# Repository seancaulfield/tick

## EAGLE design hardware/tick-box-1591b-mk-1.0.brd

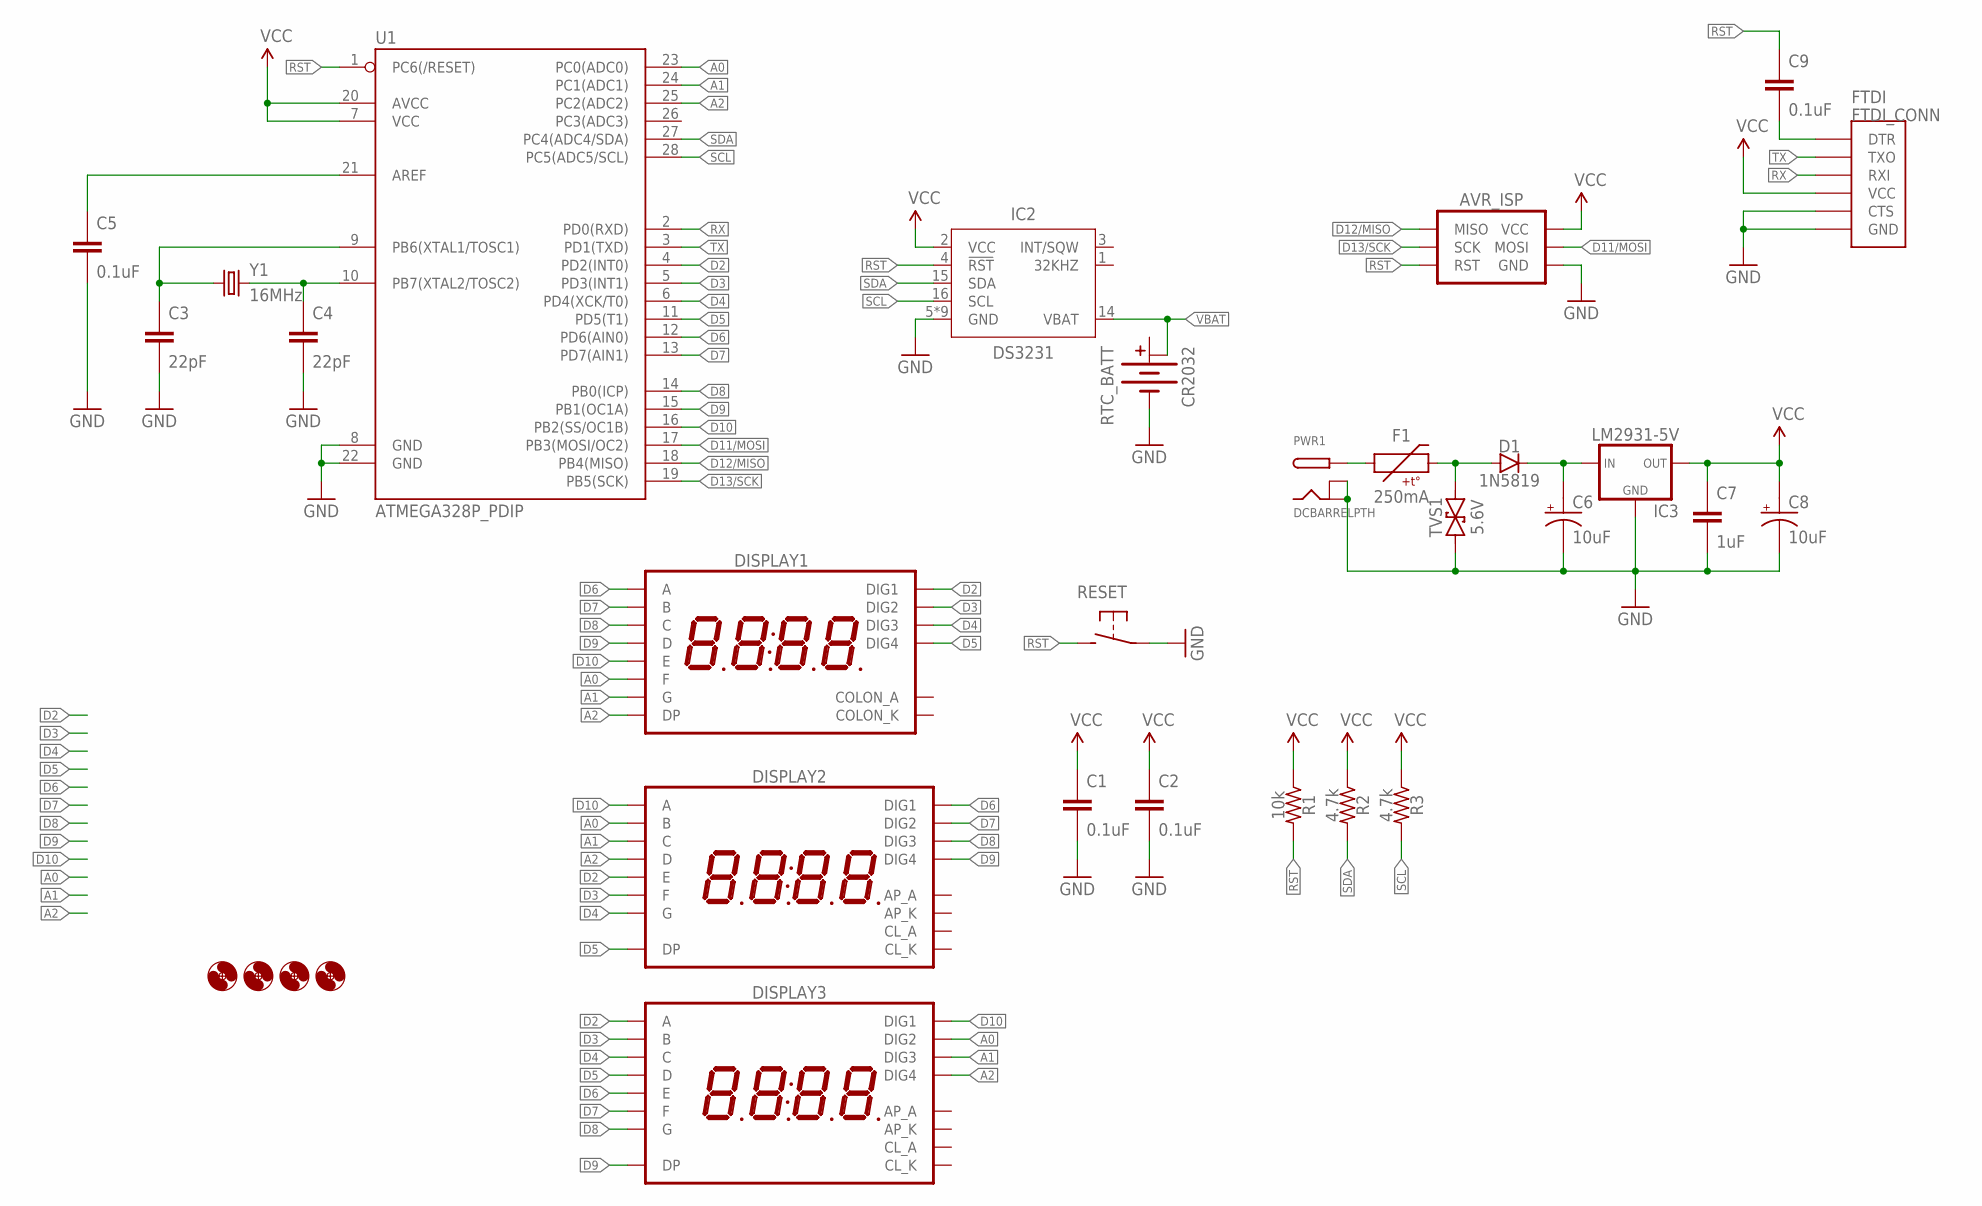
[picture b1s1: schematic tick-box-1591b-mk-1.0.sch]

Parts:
AVR_ISP: AVR_SPI_PRG_6PTH; 2X3
C1, C2, C5, C9: 0.1uF; C025-024X044
C3, C4: 22pF; C025-024X044
C6, C8: 10uF; E2-5
C7: 1uF; C025-024X044
D1: 1N5819; DIODE-10.16MM
DISPLAY1: 7SEG_4DIGIT_COLON14.2MM-CC-NS; 7SEG_4DIG_NS
DISPLAY2, DISPLAY3: 7SEG_4DIGIT_COLON_APOS; 7SEG_4DIG_10MM
F1: 250mA; PTC-PTH-5.08MM
FTDI: FTDI_CONN
H1, H2, H3, H4: HOLE#2; HOLE-#2
IC2: DS3231; SO16W
IC3: LM2931-5V; TO220-IGO-THERMPAD
PWR1: DCBARRELPTH; DCJACK_2MM_PTH
R1: 10k; RESISTOR-AXIAL-PTH-7.62MM
R2, R3: 4.7k; RESISTOR-AXIAL-PTH-7.62MM
RESET: SPST-NO-TACT6MM-PTH-SMALL-PADS; DTS-6-SMALL-PADS
RTC_BATT: CR2032; BATTCON_20MM_MINE
TVS1: 5.6V; DO-41-TVS
U1: ATMEGA328P_PDIP; DIL28-3
Y1: 16MHz; HC49U-V

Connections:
A0: DISPLAY1.P$12 (F), DISPLAY2.16 (B), DISPLAY3.2 (DIG2), U1.23 (PC0(ADC0))
A1: DISPLAY1.P$5 (G), DISPLAY2.13 (C), DISPLAY3.6 (DIG3), U1.24 (PC1(ADC1))
A2: DISPLAY1.P$3 (DP), DISPLAY2.3 (D), DISPLAY3.8 (DIG4), U1.25 (PC2(ADC2))
D2: DISPLAY1.P$14 (DIG1), DISPLAY2.5 (E), DISPLAY3.14 (A), U1.4 (PD2(INT0))
D3: DISPLAY1.P$11 (DIG2), DISPLAY2.11 (F), DISPLAY3.16 (B), U1.5 (PD3(INT1))
D4: DISPLAY1.P$10 (DIG3), DISPLAY2.15 (G), DISPLAY3.13 (C), U1.6 (PD4(XCK/T0))
D5: DISPLAY1.P$6 (DIG4), DISPLAY2.7 (DP), DISPLAY3.3 (D), U1.11 (PD5(T1))
D6: DISPLAY1.P$13 (A), DISPLAY2.1 (DIG1), DISPLAY3.5 (E), U1.12 (PD6(AIN0))
D7: DISPLAY1.P$9 (B), DISPLAY2.2 (DIG2), DISPLAY3.11 (F), U1.13 (PD7(AIN1))
D8: DISPLAY1.P$4 (C), DISPLAY2.6 (DIG3), DISPLAY3.15 (G), U1.14 (PB0(ICP))
D9: DISPLAY1.P$2 (D), DISPLAY2.8 (DIG4), DISPLAY3.7 (DP), U1.15 (PB1(OC1A))
D10: DISPLAY1.P$1 (E), DISPLAY2.14 (A), DISPLAY3.1 (DIG1), U1.16 (PB2(SS/OC1B))
D11/MOSI: AVR_ISP.4 (MOSI), U1.17 (PB3(MOSI/OC2))
D12/MISO: AVR_ISP.1 (MISO), U1.18 (PB4(MISO))
D13/SCK: AVR_ISP.3 (SCK), U1.19 (PB5(SCK))
GND: AVR_ISP.6 (GND), C1.2, C2.2, C3.2, C4.2, C5.2, C6.-, C7.2, C8.-, FTDI.CTS, FTDI.GND, IC2.5 (GND), IC2.6 (GND), IC2.7 (GND), IC2.8 (GND), IC2.9 (GND), IC2.10 (GND), IC2.11 (GND), IC2.12 (GND), IC2.13 (GND), IC3.4 (GND), IC3.GND, PWR1.BRK, PWR1.GND, RESET.1, RESET.2 (1), RTC_BATT.BOTTOM (-), TVS1.P$1 (1), U1.8 (GND), U1.22 (GND)
unnamed: C4.1, U1.10 (PB7(XTAL2/TOSC2)), Y1.2
unnamed: C3.1, U1.9 (PB6(XTAL1/TOSC1)), Y1.1
unnamed: C6.+, D1.C, IC3.IN
unnamed: F1.P$1 (1), PWR1.PWR
unnamed: C5.1, U1.21 (AREF)
unnamed: D1.A, F1.P$2 (2), TVS1.P$2 (2)
unnamed: C9.2, FTDI.DTR
RST: AVR_ISP.5 (RST), C9.1, IC2.4 (!RST), R1.P$2 (2), RESET.3 (2), RESET.4 (2), U1.1 (PC6(/RESET))
RX: FTDI.RXI, U1.2 (PD0(RXD))
SCL: IC2.16 (SCL), R3.P$2 (2), U1.28 (PC5(ADC5/SCL))
SDA: IC2.15 (SDA), R2.P$2 (2), U1.27 (PC4(ADC4/SDA))
TX: FTDI.TXO, U1.3 (PD1(TXD))
VBAT: IC2.14 (VBAT), RTC_BATT.TOP@2 (+1)
VCC: AVR_ISP.2 (VCC), C1.1, C2.1, C7.1, C8.+, FTDI.VCC, IC2.2 (VCC), IC3.OUT, R1.P$1 (1), R2.P$1 (1), R3.P$1 (1), U1.7 (VCC), U1.20 (AVCC)

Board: 2 copper layers, 31 parts (1 on the bottom side), 30 nets, no tracks yet.

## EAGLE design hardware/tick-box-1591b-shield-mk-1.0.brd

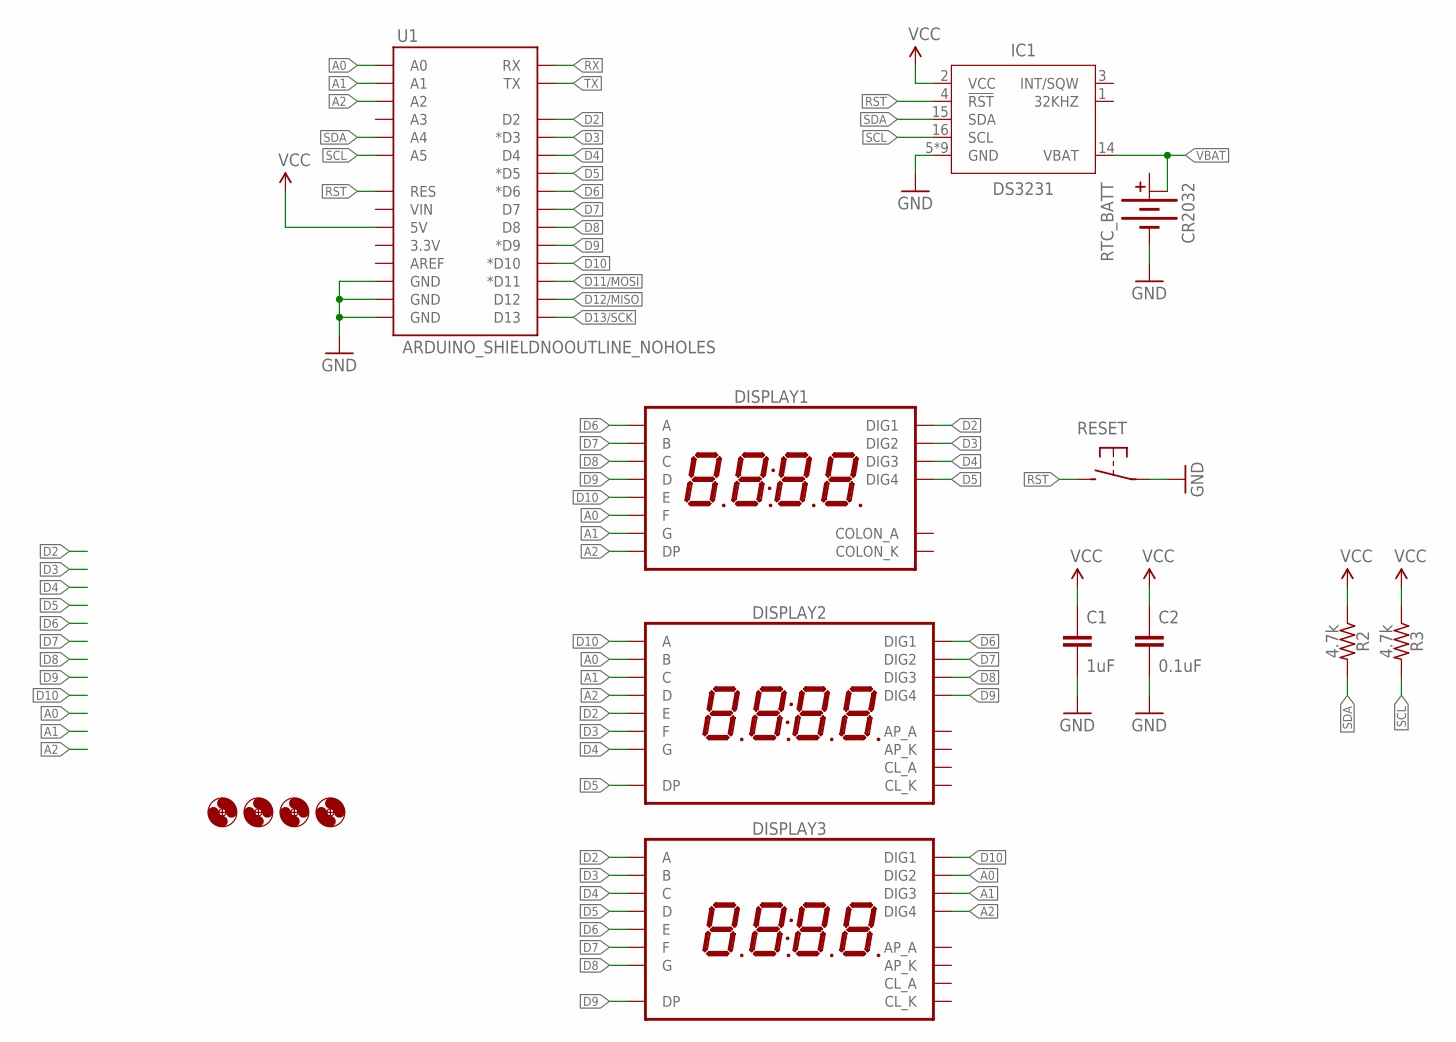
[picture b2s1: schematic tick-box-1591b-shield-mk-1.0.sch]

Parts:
C1: 1uF; C025-024X044
C2: 0.1uF; C025-024X044
DISPLAY1: 7SEG_4DIGIT_COLON14.2MM-CC-NS; 7SEG_4DIG_NS
DISPLAY2, DISPLAY3: 7SEG_4DIGIT_COLON_APOS; 7SEG_4DIG_10MM
H1, H2, H3, H4: HOLE#2; HOLE-#2
IC1: DS3231; SO16W
R2, R3: 4.7k; RESISTOR-AXIAL-PTH-7.62MM
RESET: SPST-NO-TACT6MM-PTH-SMALL-PADS; DTS-6-SMALL-PADS
RTC_BATT: CR2032; BATTCON_20MM_MINE
U1: ARDUINO_SHIELDNOOUTLINE_NOHOLES; ARDUINO_SHIELD_NOOUTLINE_NOHOLES

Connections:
A0: DISPLAY1.P$12 (F), DISPLAY2.16 (B), DISPLAY3.2 (DIG2), U1.A0
A1: DISPLAY1.P$5 (G), DISPLAY2.13 (C), DISPLAY3.6 (DIG3), U1.A1
A2: DISPLAY1.P$3 (DP), DISPLAY2.3 (D), DISPLAY3.8 (DIG4), U1.A2
D2: DISPLAY1.P$14 (DIG1), DISPLAY2.5 (E), DISPLAY3.14 (A), U1.D2
D3: DISPLAY1.P$11 (DIG2), DISPLAY2.11 (F), DISPLAY3.16 (B), U1.D3 (*D3)
D4: DISPLAY1.P$10 (DIG3), DISPLAY2.15 (G), DISPLAY3.13 (C), U1.D4
D5: DISPLAY1.P$6 (DIG4), DISPLAY2.7 (DP), DISPLAY3.3 (D), U1.D5 (*D5)
D6: DISPLAY1.P$13 (A), DISPLAY2.1 (DIG1), DISPLAY3.5 (E), U1.D6 (*D6)
D7: DISPLAY1.P$9 (B), DISPLAY2.2 (DIG2), DISPLAY3.11 (F), U1.D7
D8: DISPLAY1.P$4 (C), DISPLAY2.6 (DIG3), DISPLAY3.15 (G), U1.D8
D9: DISPLAY1.P$2 (D), DISPLAY2.8 (DIG4), DISPLAY3.7 (DP), U1.D9 (*D9)
D10: DISPLAY1.P$1 (E), DISPLAY2.14 (A), DISPLAY3.1 (DIG1), U1.D10 (*D10)
D11/MOSI: U1.D11 (*D11)
D12/MISO: U1.D12
D13/SCK: U1.D13
GND: C1.2, C2.2, IC1.5 (GND), IC1.6 (GND), IC1.7 (GND), IC1.8 (GND), IC1.9 (GND), IC1.10 (GND), IC1.11 (GND), IC1.12 (GND), IC1.13 (GND), RESET.1, RESET.2 (1), RTC_BATT.BOTTOM (-), U1.GND@0 (GND), U1.GND@1 (GND), U1.GND@2 (GND)
RST: IC1.4 (!RST), RESET.3 (2), RESET.4 (2), U1.RES
RX: U1.RX
SCL: IC1.16 (SCL), R3.P$2 (2), U1.A5
SDA: IC1.15 (SDA), R2.P$2 (2), U1.A4
TX: U1.TX
VBAT: IC1.14 (VBAT), RTC_BATT.TOP@2 (+1)
VCC: C1.1, C2.1, IC1.2 (VCC), R2.P$1 (1), R3.P$1 (1), U1.5V

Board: 2 copper layers, 15 parts (0 on the bottom side), 18 nets, no tracks yet.

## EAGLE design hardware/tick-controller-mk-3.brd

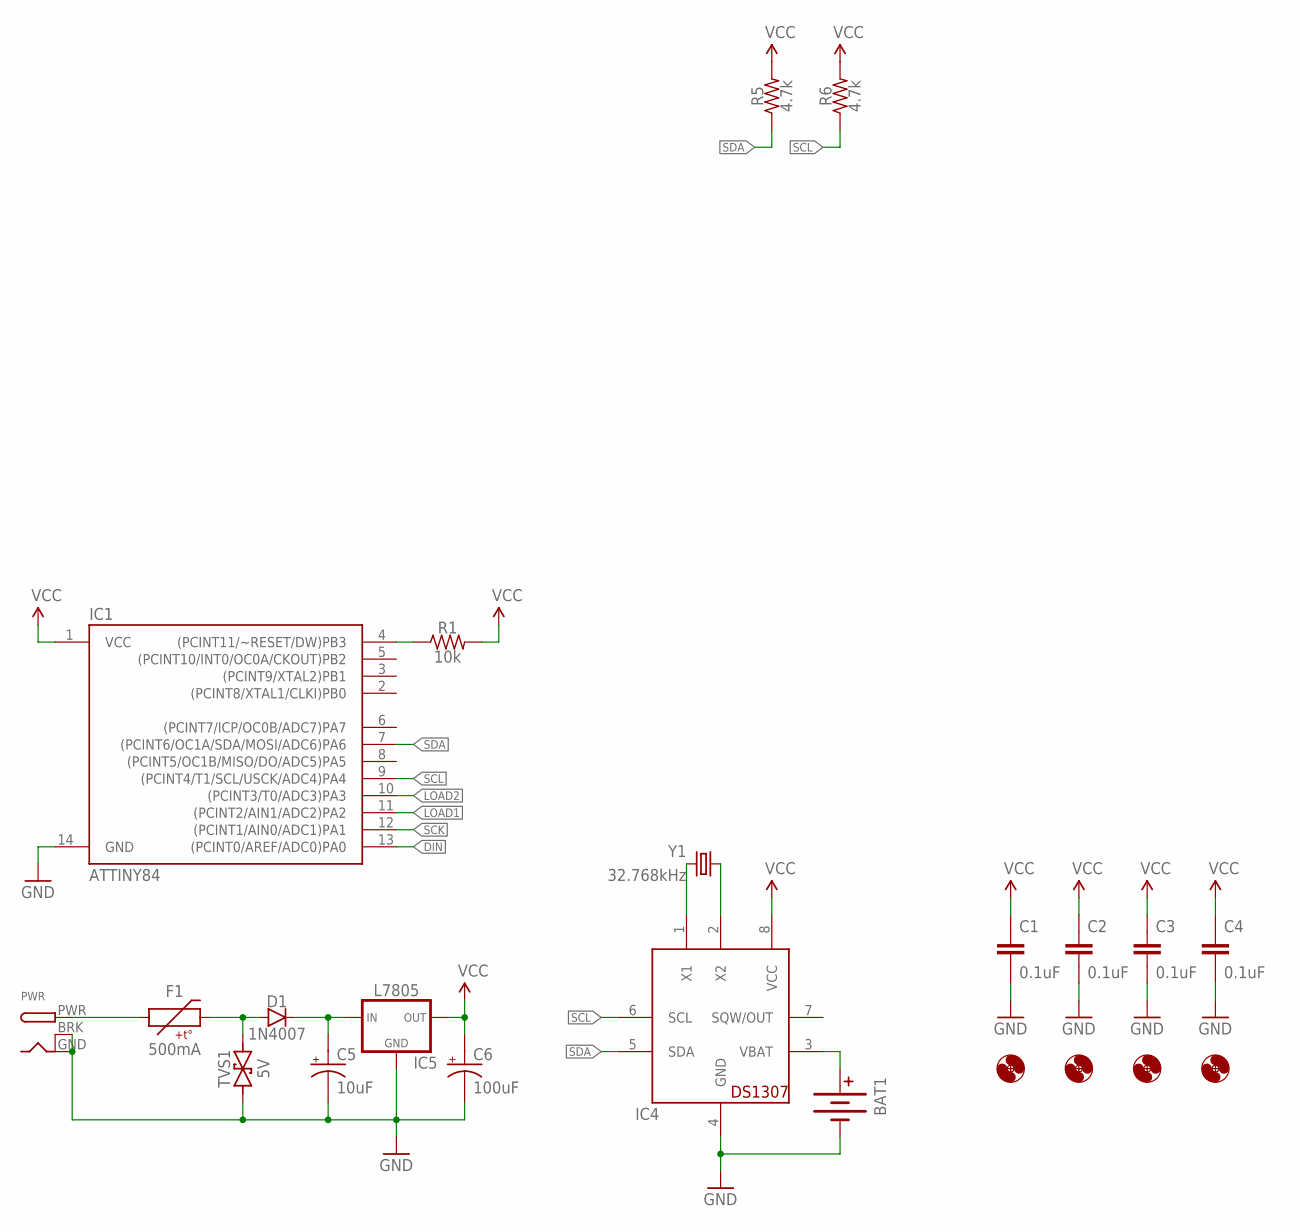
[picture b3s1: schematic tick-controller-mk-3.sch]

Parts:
BAT1: BATTERY20SMD; BATTCON_20MM
C1, C2, C3, C4: 0.1uF; C025-024X044
C5: 10uF; E2-5
C6: 100uF; E2-5
D1: 1N4007; DIODE-10.16MM
F1: 500mA; PTC-PTH-5.08MM
H1, H2, H3, H4: HOLE#2; HOLE-#2
IC1: ATTINY84; DIL14
IC4: DS1307; DIL08
IC5: L7805; TO-92-AMMO
PWR: DCBARRELPTH; DCJACK_2MM_PTH
R1: 10k; RESISTOR-AXIAL-PTH-5.08MM
R5, R6: 4.7k; RESISTOR-AXIAL-PTH-5.08MM
TVS1: 5V; DO-41-TVS-BI-10.16MM
Y1: 32.768kHz; TC26H

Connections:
DIN: IC1.13 ((PCINT0/AREF/ADC0)PA0)
GND: BAT1.2 (-), C1.2, C2.2, C3.2, C4.2, C5.-, C6.-, IC1.14 (GND), IC4.4 (GND), IC5.2 (GND), PWR.BRK, PWR.GND, TVS1.P$1 (1)
LOAD1: IC1.11 ((PCINT2/AIN1/ADC2)PA2)
LOAD2: IC1.10 ((PCINT3/T0/ADC3)PA3)
unnamed: IC1.4 ((PCINT11/~RESET/DW)PB3), R1.P$1 (1)
unnamed: IC4.1 (X1), Y1.2
unnamed: BAT1.1 (+), BAT1.3 (+), IC4.3 (VBAT)
unnamed: IC4.2 (X2), Y1.1
unnamed: C5.+, D1.C, IC5.1 (IN)
unnamed: F1.P$1 (1), PWR.PWR
unnamed: D1.A, F1.P$2 (2), TVS1.P$2 (2)
SCK: IC1.12 ((PCINT1/AIN0/ADC1)PA1)
SCL: IC1.9 ((PCINT4/T1/SCL/USCK/ADC4)PA4), IC4.6 (SCL), R6.P$1 (1)
SDA: IC1.7 ((PCINT6/OC1A/SDA/MOSI/ADC6)PA6), IC4.5 (SDA), R5.P$1 (1)
VCC: C1.1, C2.1, C3.1, C4.1, C6.+, IC1.1 (VCC), IC4.8 (VCC), IC5.3 (OUT), R1.P$2 (2), R5.P$2 (2), R6.P$2 (2)

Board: 2 copper layers, 22 parts (0 on the bottom side), 11 nets, no tracks yet.

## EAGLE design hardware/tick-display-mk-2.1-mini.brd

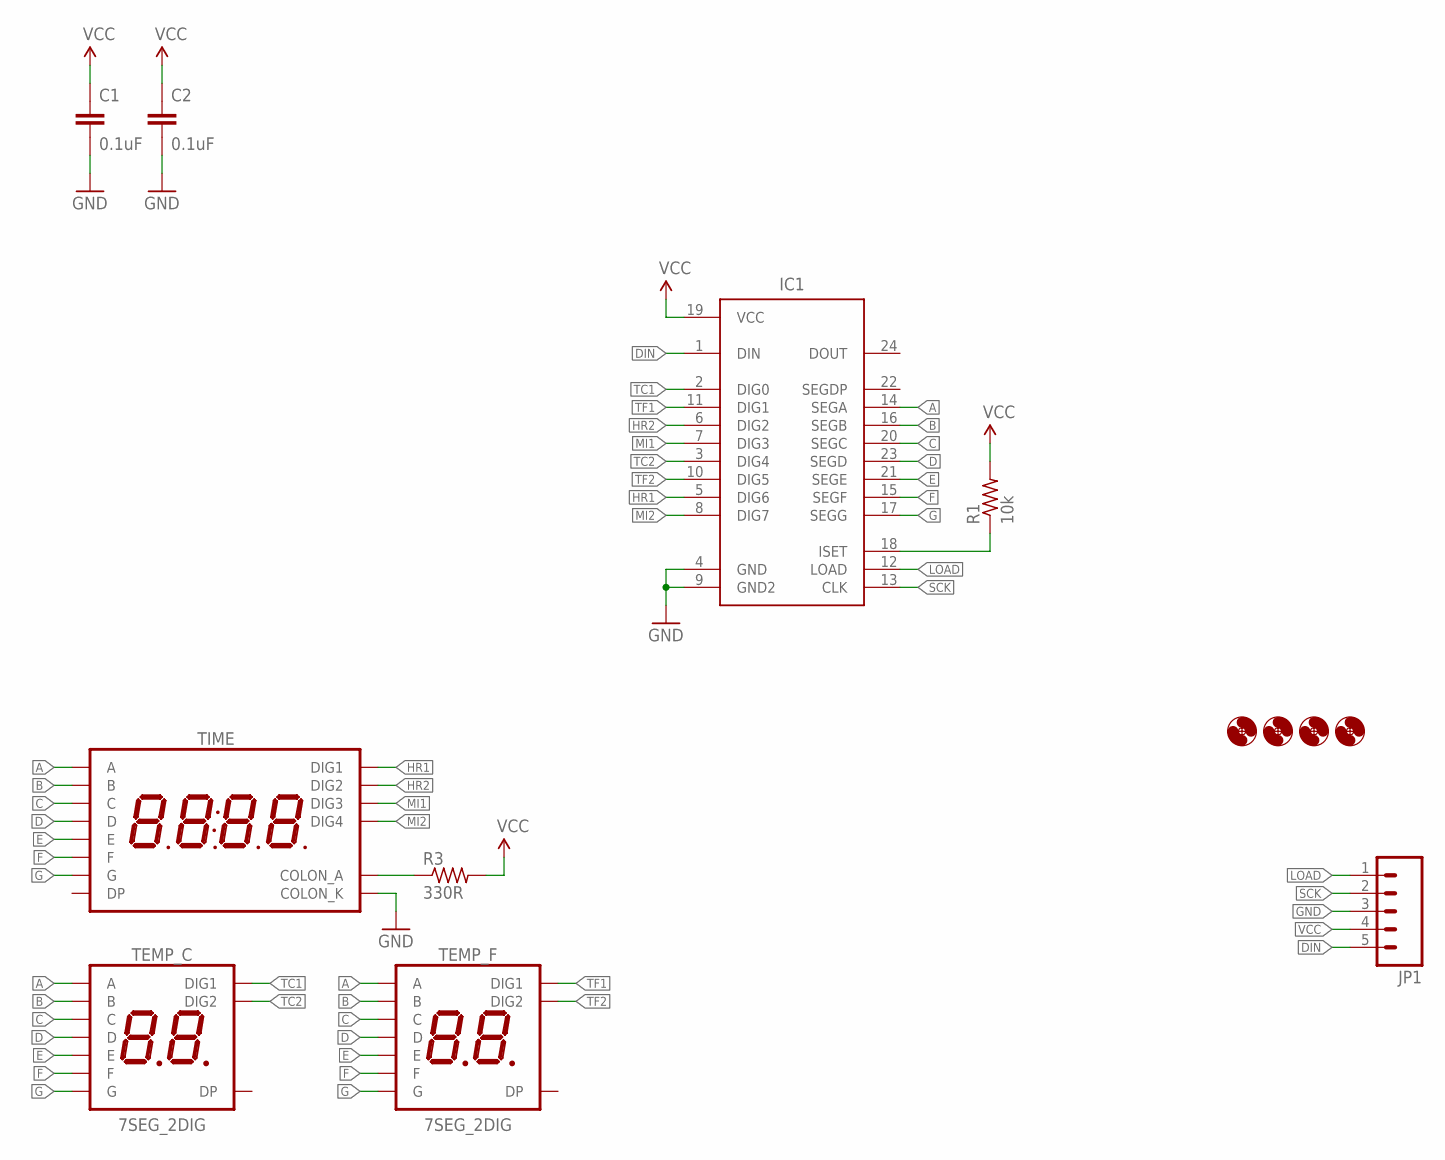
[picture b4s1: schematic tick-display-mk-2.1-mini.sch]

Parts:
C1, C2: 0.1uF; C025-024X044
H1, H2, H3, H4: HOLE#2; HOLE-#2
IC1: MAX7219DIP; DIL24
JP1: M05JST-PH-VERT-PTH; JST-5-PH-VERT-PTH
R1: 10k; RESISTOR-AXIAL-PTH-5.08MM
R3: 330R; RESISTOR-AXIAL-PTH-5.08MM
TEMP_C: 7SEG_2DIG; 7SEG_2DIG_14MM
TEMP_F: 7SEG_2DIG; 7SEG_2DIG_14MM
TIME: 7SED_4DIGIT_14MM14.2MM-CC; 7SEG_4DIG

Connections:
A: IC1.14 (SEGA), TEMP_C.4 (A), TEMP_F.4 (A), TIME.P$13 (A)
B: IC1.16 (SEGB), TEMP_C.3 (B), TEMP_F.3 (B), TIME.P$9 (B)
C: IC1.20 (SEGC), TEMP_C.9 (C), TEMP_F.9 (C), TIME.P$4 (C)
D: IC1.23 (SEGD), TEMP_C.8 (D), TEMP_F.8 (D), TIME.P$2 (D)
DIN: IC1.1 (DIN), JP1.5
E: IC1.21 (SEGE), TEMP_C.6 (E), TEMP_F.6 (E), TIME.P$1 (E)
F: IC1.15 (SEGF), TEMP_C.7 (F), TEMP_F.7 (F), TIME.P$12 (F)
G: IC1.17 (SEGG), TEMP_C.1 (G), TEMP_F.1 (G), TIME.P$5 (G)
GND: C1.2, C2.2, IC1.4 (GND), IC1.9 (GND2), JP1.3, TIME.P$7 (COLON_K)
HR1: IC1.5 (DIG6), TIME.P$14 (DIG1)
HR2: IC1.6 (DIG2), TIME.P$11 (DIG2)
LOAD: IC1.12 (LOAD), JP1.1
MI1: IC1.7 (DIG3), TIME.P$10 (DIG3)
MI2: IC1.8 (DIG7), TIME.P$6 (DIG4)
unnamed: IC1.18 (ISET), R1.P$1 (1)
unnamed: R3.P$1 (1), TIME.P$8 (COLON_A)
SCK: IC1.13 (CLK), JP1.2
TC1: IC1.2 (DIG0), TEMP_C.5 (DIG1)
TC2: IC1.3 (DIG4), TEMP_C.10 (DIG2)
TF1: IC1.11 (DIG1), TEMP_F.5 (DIG1)
TF2: IC1.10 (DIG5), TEMP_F.10 (DIG2)
VCC: C1.1, C2.1, IC1.19 (VCC), JP1.4, R1.P$2 (2), R3.P$2 (2)

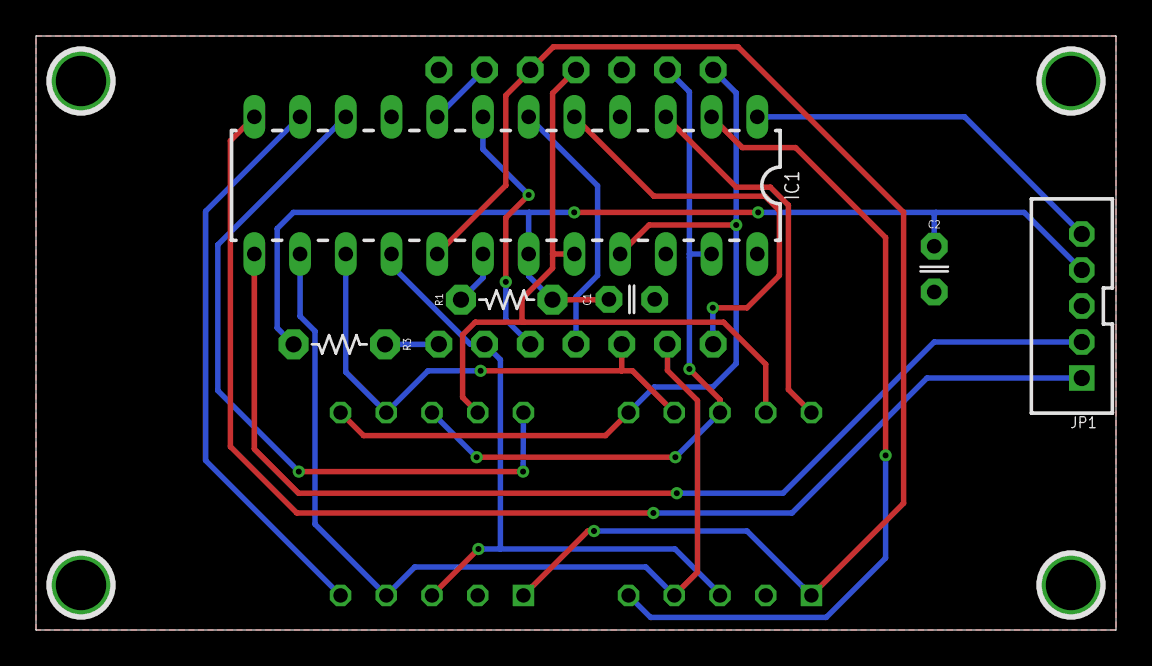
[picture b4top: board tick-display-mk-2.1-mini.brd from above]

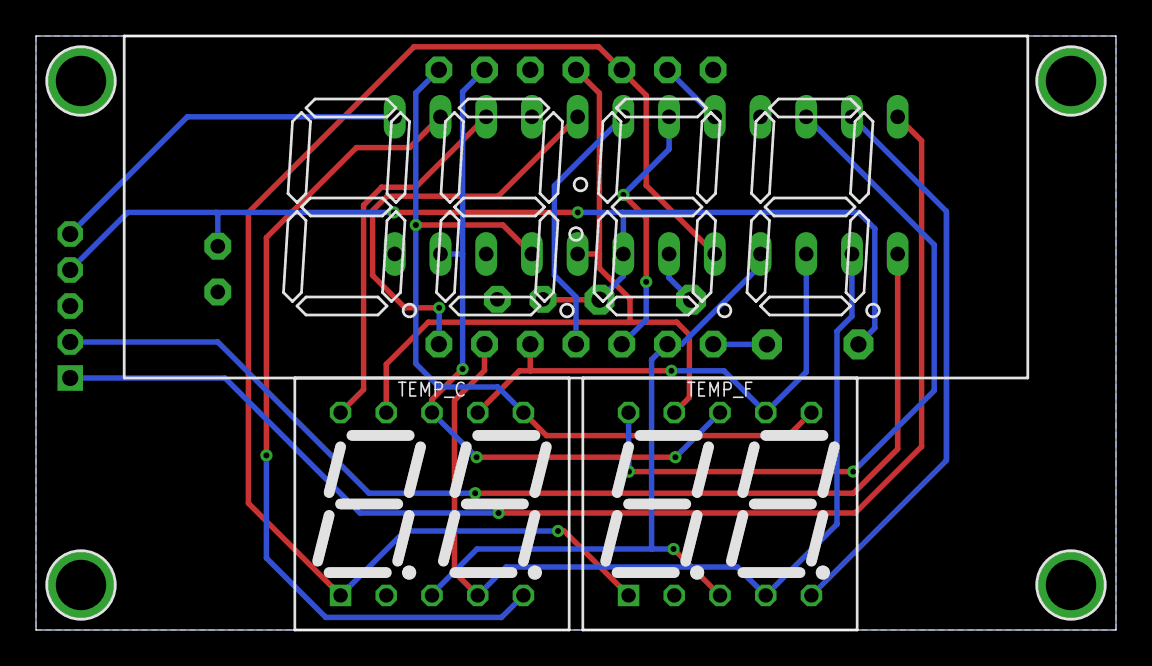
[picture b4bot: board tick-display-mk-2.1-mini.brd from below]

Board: 2 copper layers, 60.0 x 33.0 mm, 13 parts (3 on the bottom side), 22 nets.

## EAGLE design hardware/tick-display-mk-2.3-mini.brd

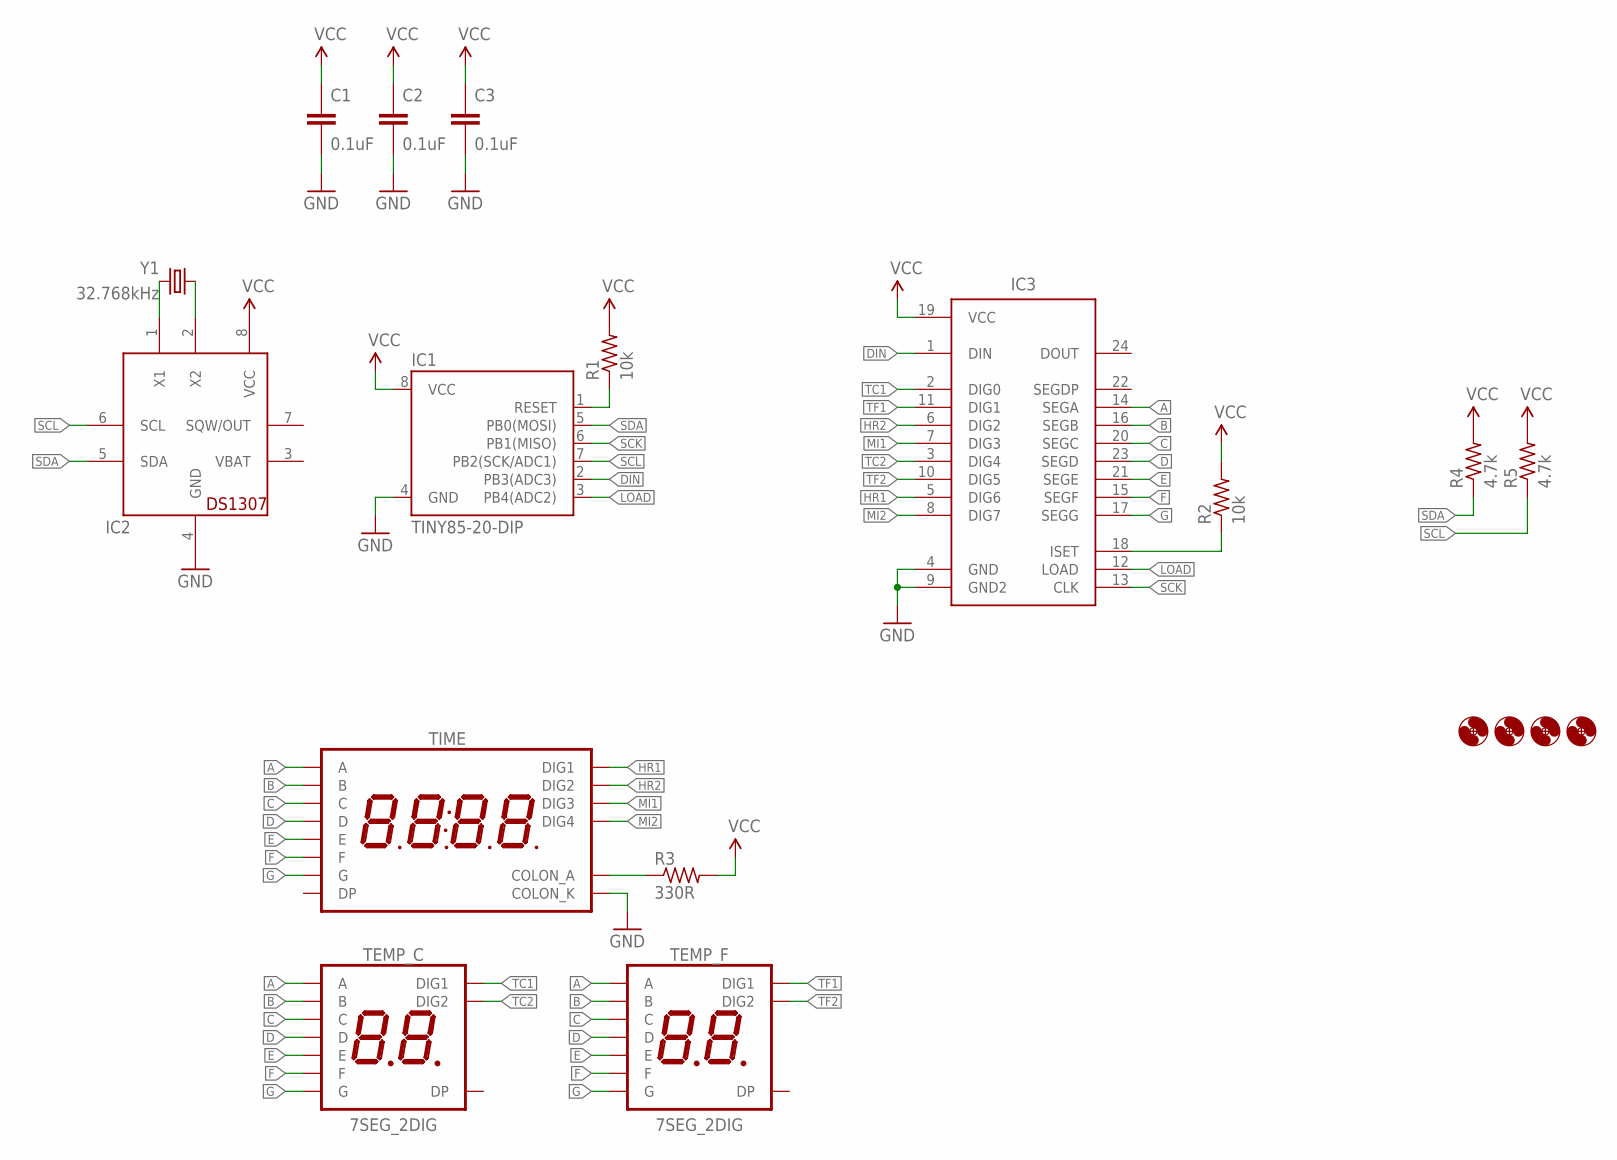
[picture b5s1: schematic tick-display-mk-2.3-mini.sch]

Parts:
C1, C2, C3: 0.1uF; C025-024X044
H1, H2, H3, H4: HOLE#2; HOLE-#2
IC1: TINY85-20-DIP; DIP08
IC2: DS1307; DIL08
IC3: MAX7219DIP; DIL24
R1, R2: 10k; RESISTOR-AXIAL-PTH-5.08MM
R3: 330R; RESISTOR-AXIAL-PTH-5.08MM
R4, R5: 4.7k; RESISTOR-AXIAL-PTH-5.08MM
TEMP_C: 7SEG_2DIG; 7SEG_2DIG_14MM
TEMP_F: 7SEG_2DIG; 7SEG_2DIG_14MM
TIME: 7SED_4DIGIT_14MM14.2MM-CC; 7SEG_4DIG
Y1: 32.768kHz; TC26H

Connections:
A: IC3.14 (SEGA), TEMP_C.4 (A), TEMP_F.4 (A), TIME.P$13 (A)
B: IC3.16 (SEGB), TEMP_C.3 (B), TEMP_F.3 (B), TIME.P$9 (B)
C: IC3.20 (SEGC), TEMP_C.9 (C), TEMP_F.9 (C), TIME.P$4 (C)
D: IC3.23 (SEGD), TEMP_C.8 (D), TEMP_F.8 (D), TIME.P$2 (D)
DIN: IC1.2 (PB3(ADC3)), IC3.1 (DIN)
E: IC3.21 (SEGE), TEMP_C.6 (E), TEMP_F.6 (E), TIME.P$1 (E)
F: IC3.15 (SEGF), TEMP_C.7 (F), TEMP_F.7 (F), TIME.P$12 (F)
G: IC3.17 (SEGG), TEMP_C.1 (G), TEMP_F.1 (G), TIME.P$5 (G)
GND: C1.2, C2.2, C3.2, IC1.4 (GND), IC2.4 (GND), IC3.4 (GND), IC3.9 (GND2), TIME.P$7 (COLON_K)
HR1: IC3.5 (DIG6), TIME.P$14 (DIG1)
HR2: IC3.6 (DIG2), TIME.P$11 (DIG2)
LOAD: IC1.3 (PB4(ADC2)), IC3.12 (LOAD)
MI1: IC3.7 (DIG3), TIME.P$10 (DIG3)
MI2: IC3.8 (DIG7), TIME.P$6 (DIG4)
unnamed: IC3.18 (ISET), R2.P$1 (1)
unnamed: IC1.1 (RESET), R1.P$1 (1)
unnamed: IC2.1 (X1), Y1.2
unnamed: IC2.2 (X2), Y1.1
unnamed: R3.P$1 (1), TIME.P$8 (COLON_A)
SCK: IC1.6 (PB1(MISO)), IC3.13 (CLK)
SCL: IC1.7 (PB2(SCK/ADC1)), IC2.6 (SCL), R5.P$1 (1)
SDA: IC1.5 (PB0(MOSI)), IC2.5 (SDA), R4.P$1 (1)
TC1: IC3.2 (DIG0), TEMP_C.5 (DIG1)
TC2: IC3.3 (DIG4), TEMP_C.10 (DIG2)
TF1: IC3.11 (DIG1), TEMP_F.5 (DIG1)
TF2: IC3.10 (DIG5), TEMP_F.10 (DIG2)
VBAT: IC2.3 (VBAT)
VCC: C1.1, C2.1, C3.1, IC1.8 (VCC), IC2.8 (VCC), IC3.19 (VCC), R1.P$2 (2), R2.P$2 (2), R3.P$2 (2), R4.P$2 (2), R5.P$2 (2)

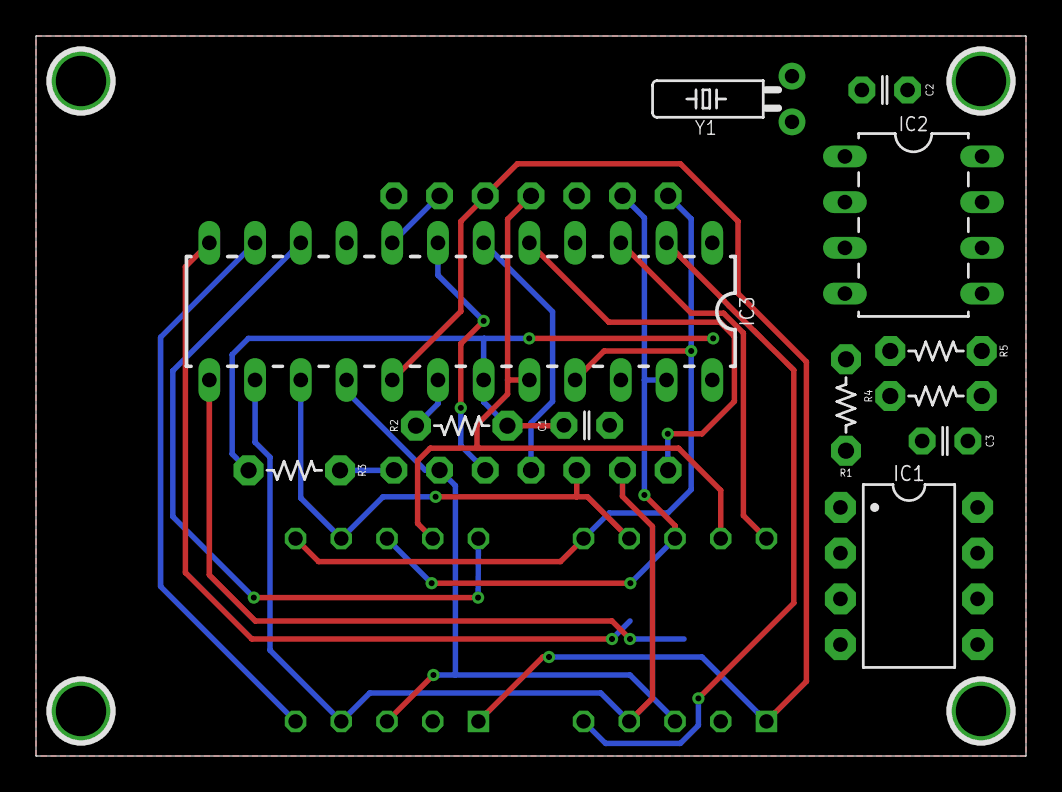
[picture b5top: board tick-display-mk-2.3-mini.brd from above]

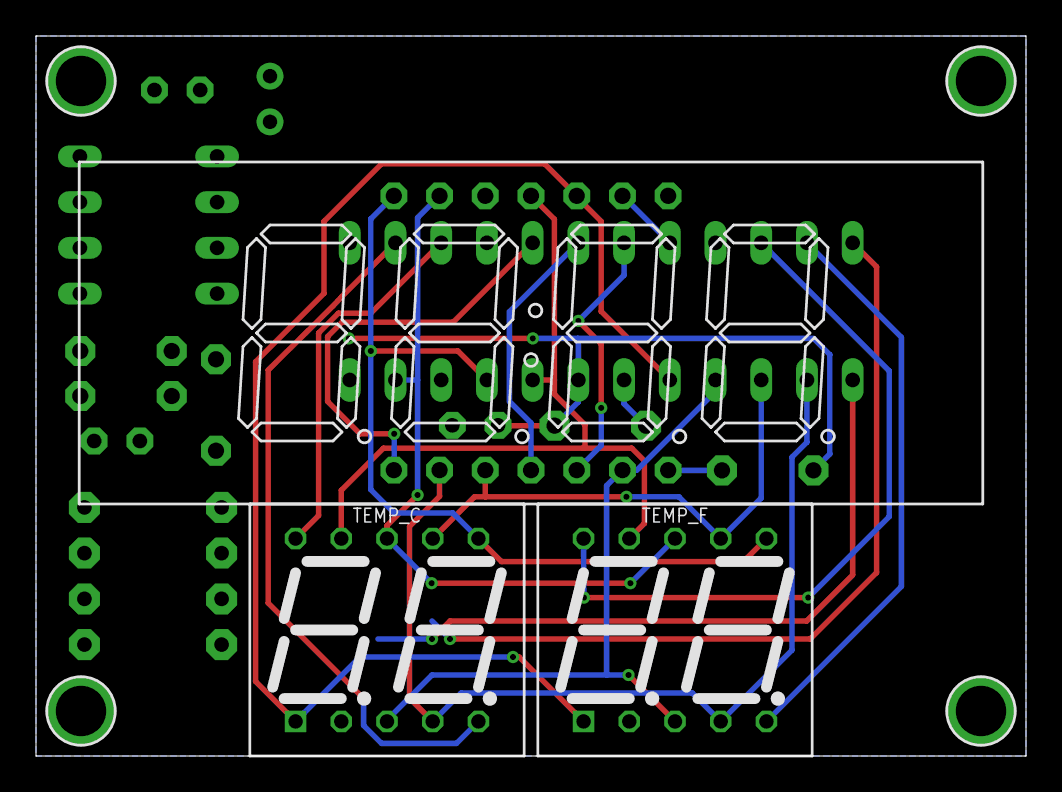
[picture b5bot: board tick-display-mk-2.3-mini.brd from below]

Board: 2 copper layers, 55.0 x 40.0 mm, 19 parts (3 on the bottom side), 27 nets.

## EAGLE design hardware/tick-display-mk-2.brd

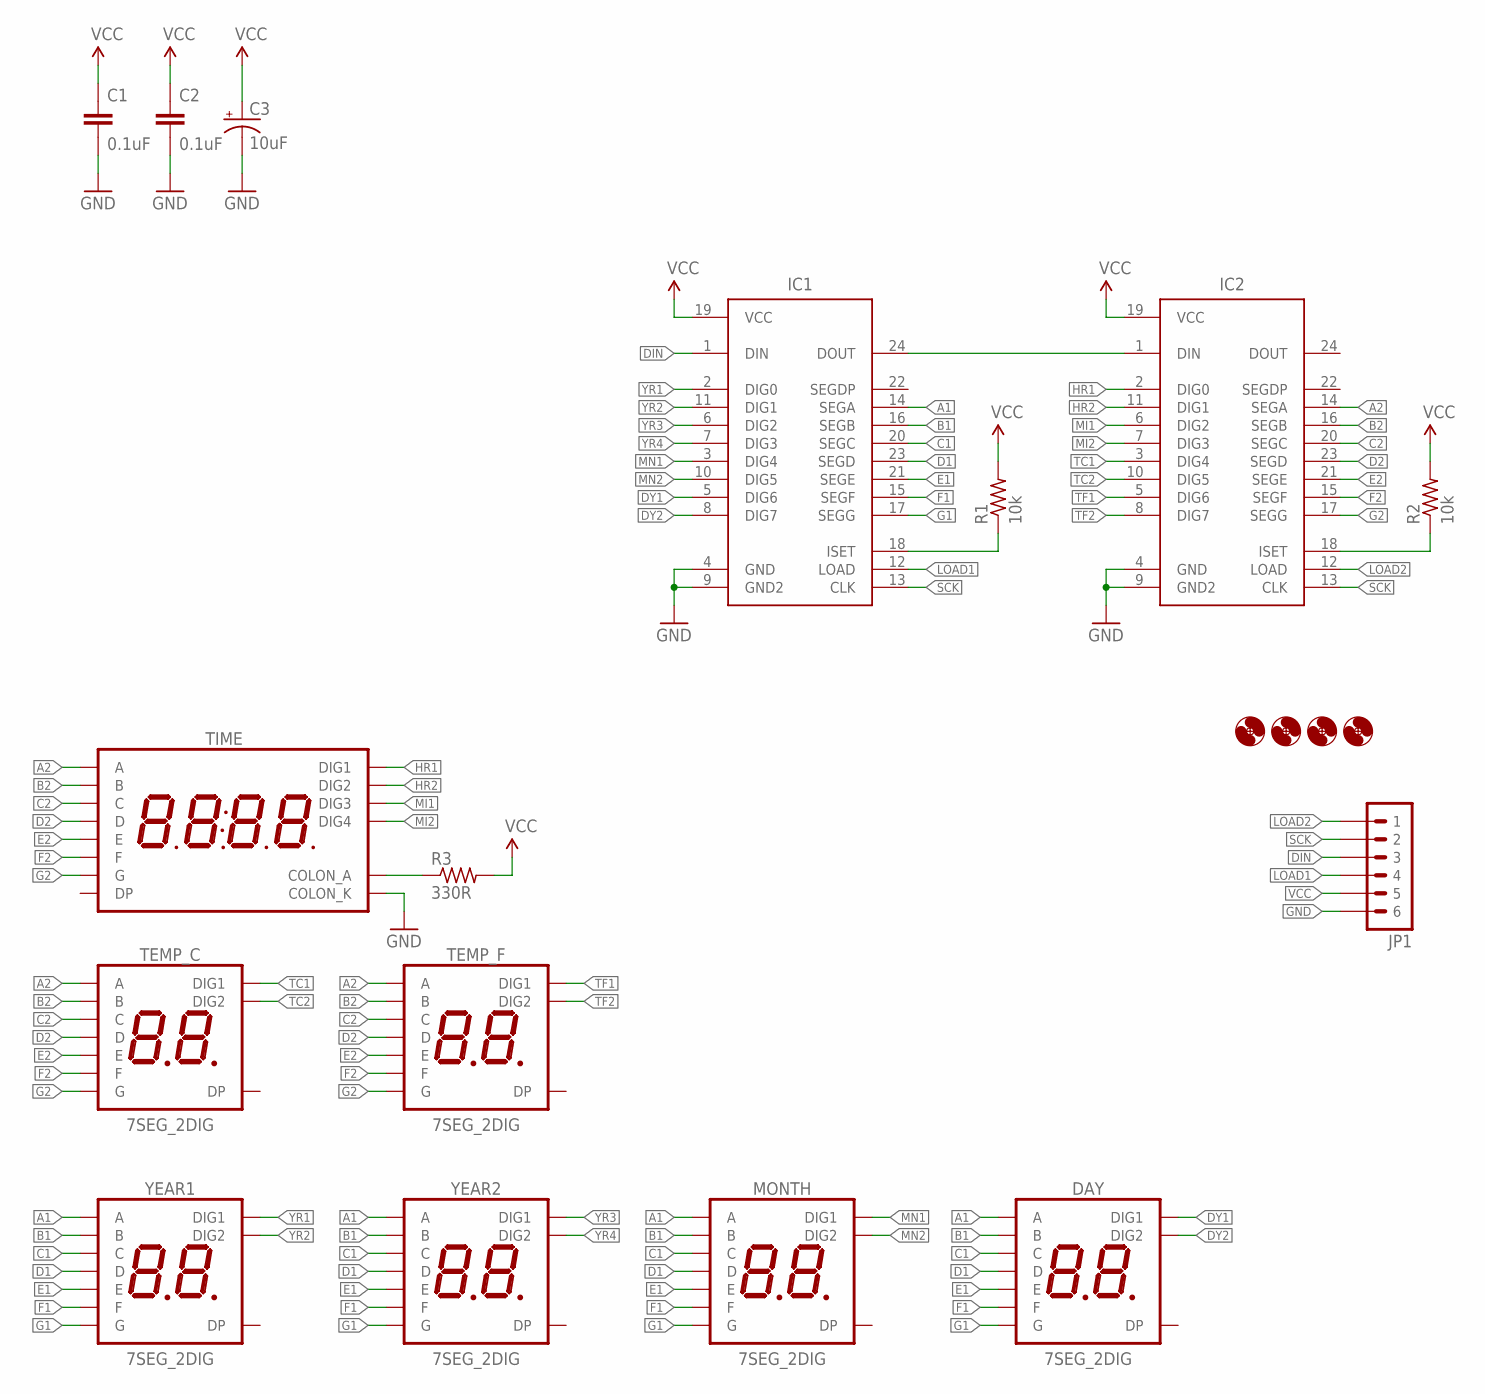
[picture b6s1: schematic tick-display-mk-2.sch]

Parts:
C1, C2: 0.1uF; C025-024X044
C3: 10uF; E2-5
DAY: 7SEG_2DIG; 7SEG_2DIG_14MM
H1, H2, H3, H4: HOLE#2; HOLE-#2
IC1, IC2: MAX7219; DIL24
JP1: M06JST-PH-PTH-VERT; JST-6-PH-VERT-PTH
MONTH: 7SEG_2DIG; 7SEG_2DIG_14MM
R1, R2: 10k; RESISTOR-AXIAL-PTH-5.08MM
R3: 330R; RESISTOR-AXIAL-PTH-5.08MM
TEMP_C: 7SEG_2DIG; 7SEG_2DIG_14MM
TEMP_F: 7SEG_2DIG; 7SEG_2DIG_14MM
TIME: 7SED_4DIGIT_14MM14.2MM-CC; 7SEG_4DIG
YEAR1, YEAR2: 7SEG_2DIG; 7SEG_2DIG_14MM

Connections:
A1: DAY.4 (A), IC1.14 (SEGA), MONTH.4 (A), YEAR1.4 (A), YEAR2.4 (A)
A2: IC2.14 (SEGA), TEMP_C.4 (A), TEMP_F.4 (A), TIME.P$13 (A)
B1: DAY.3 (B), IC1.16 (SEGB), MONTH.3 (B), YEAR1.3 (B), YEAR2.3 (B)
B2: IC2.16 (SEGB), TEMP_C.3 (B), TEMP_F.3 (B), TIME.P$9 (B)
C1: DAY.9 (C), IC1.20 (SEGC), MONTH.9 (C), YEAR1.9 (C), YEAR2.9 (C)
C2: IC2.20 (SEGC), TEMP_C.9 (C), TEMP_F.9 (C), TIME.P$4 (C)
D1: DAY.8 (D), IC1.23 (SEGD), MONTH.8 (D), YEAR1.8 (D), YEAR2.8 (D)
D2: IC2.23 (SEGD), TEMP_C.8 (D), TEMP_F.8 (D), TIME.P$2 (D)
DIN: IC1.1 (DIN), JP1.3
DY1: DAY.5 (DIG1), IC1.5 (DIG6)
DY2: DAY.10 (DIG2), IC1.8 (DIG7)
E1: DAY.6 (E), IC1.21 (SEGE), MONTH.6 (E), YEAR1.6 (E), YEAR2.6 (E)
E2: IC2.21 (SEGE), TEMP_C.6 (E), TEMP_F.6 (E), TIME.P$1 (E)
F1: DAY.7 (F), IC1.15 (SEGF), MONTH.7 (F), YEAR1.7 (F), YEAR2.7 (F)
F2: IC2.15 (SEGF), TEMP_C.7 (F), TEMP_F.7 (F), TIME.P$12 (F)
G1: DAY.1 (G), IC1.17 (SEGG), MONTH.1 (G), YEAR1.1 (G), YEAR2.1 (G)
G2: IC2.17 (SEGG), TEMP_C.1 (G), TEMP_F.1 (G), TIME.P$5 (G)
GND: C1.2, C2.2, C3.-, IC1.4 (GND), IC1.9 (GND2), IC2.4 (GND), IC2.9 (GND2), JP1.6, TIME.P$7 (COLON_K)
HR1: IC2.2 (DIG0), TIME.P$14 (DIG1)
HR2: IC2.11 (DIG1), TIME.P$11 (DIG2)
LOAD1: IC1.12 (LOAD), JP1.4
LOAD2: IC2.12 (LOAD), JP1.1
MI1: IC2.6 (DIG2), TIME.P$10 (DIG3)
MI2: IC2.7 (DIG3), TIME.P$6 (DIG4)
MN1: IC1.3 (DIG4), MONTH.5 (DIG1)
MN2: IC1.10 (DIG5), MONTH.10 (DIG2)
unnamed: IC1.18 (ISET), R1.P$1 (1)
unnamed: IC1.24 (DOUT), IC2.1 (DIN)
unnamed: IC2.18 (ISET), R2.P$1 (1)
unnamed: R3.P$1 (1), TIME.P$8 (COLON_A)
SCK: IC1.13 (CLK), IC2.13 (CLK), JP1.2
TC1: IC2.3 (DIG4), TEMP_C.5 (DIG1)
TC2: IC2.10 (DIG5), TEMP_C.10 (DIG2)
TF1: IC2.5 (DIG6), TEMP_F.5 (DIG1)
TF2: IC2.8 (DIG7), TEMP_F.10 (DIG2)
VCC: C1.1, C2.1, C3.+, IC1.19 (VCC), IC2.19 (VCC), JP1.5, R1.P$2 (2), R2.P$2 (2), R3.P$2 (2)
YR1: IC1.2 (DIG0), YEAR1.5 (DIG1)
YR2: IC1.11 (DIG1), YEAR1.10 (DIG2)
YR3: IC1.6 (DIG2), YEAR2.5 (DIG1)
YR4: IC1.7 (DIG3), YEAR2.10 (DIG2)
